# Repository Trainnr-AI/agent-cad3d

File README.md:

# agent-cad3d

Agentic 3D design: describe what you want, and an AI agent builds it in a live Blender session
you can watch and take over at any time. Focused first on robotics: robot links, grippers,
fixtures and simulation scenes, exported to STL/OBJ/glTF and MJCF/URDF.

Built on [MCP for Blender](https://github.com/ahujasid/mcp-for-blender). Other CAD backends
(FreeCAD, SolidWorks) are planned.

**Continuing work? Read [docs/HANDOFF.md](docs/HANDOFF.md).**

## Setup (macOS / Linux / WSL2)

```bash
./scripts/setup.sh
```

This installs `uv` and Blender if missing, installs the MCP for Blender addon and enables it.
Then:

1. Open Blender. The addon's server auto-starts; this repo uses `localhost:9877` (9876 is the trainnr
   Studio viewer's port). Set the port in the addon panel and save it in your .blend. Check it in the 3D viewport:
   press `N` → **MCP for Blender** tab (click **Start MCP Server** if needed).
2. Run `claude` in this repo and approve the `blender` MCP server from `.mcp.json`.
3. Ask for something: *"Make a 2-link planar arm, 0.3 m and 0.25 m links, revolute joints about Z."*

Telemetry is disabled in `.mcp.json`. The addon only listens on localhost.

## How it works

```
you ──▶ Claude Code ──MCP (stdio)──▶ mcp-for-blender ──TCP :9877──▶ Blender addon ──▶ your scene
                ◀────────── screenshots, scene info, results ◀──────────
```

The agent writes Blender Python for modelling, reads numbers back from the scene, and takes
viewport screenshots to check its own work. Conventions it follows are in [CLAUDE.md](CLAUDE.md).

## Security note

The MCP server can run any Python inside Blender. Save your work, and only connect it to Blender
instances you trust. Set `BLENDER_MCP_SAFE_MODE=1` in `.mcp.json`'s `env` to block file, network
and subprocess access from agent scripts (normal modelling and import/export still work).

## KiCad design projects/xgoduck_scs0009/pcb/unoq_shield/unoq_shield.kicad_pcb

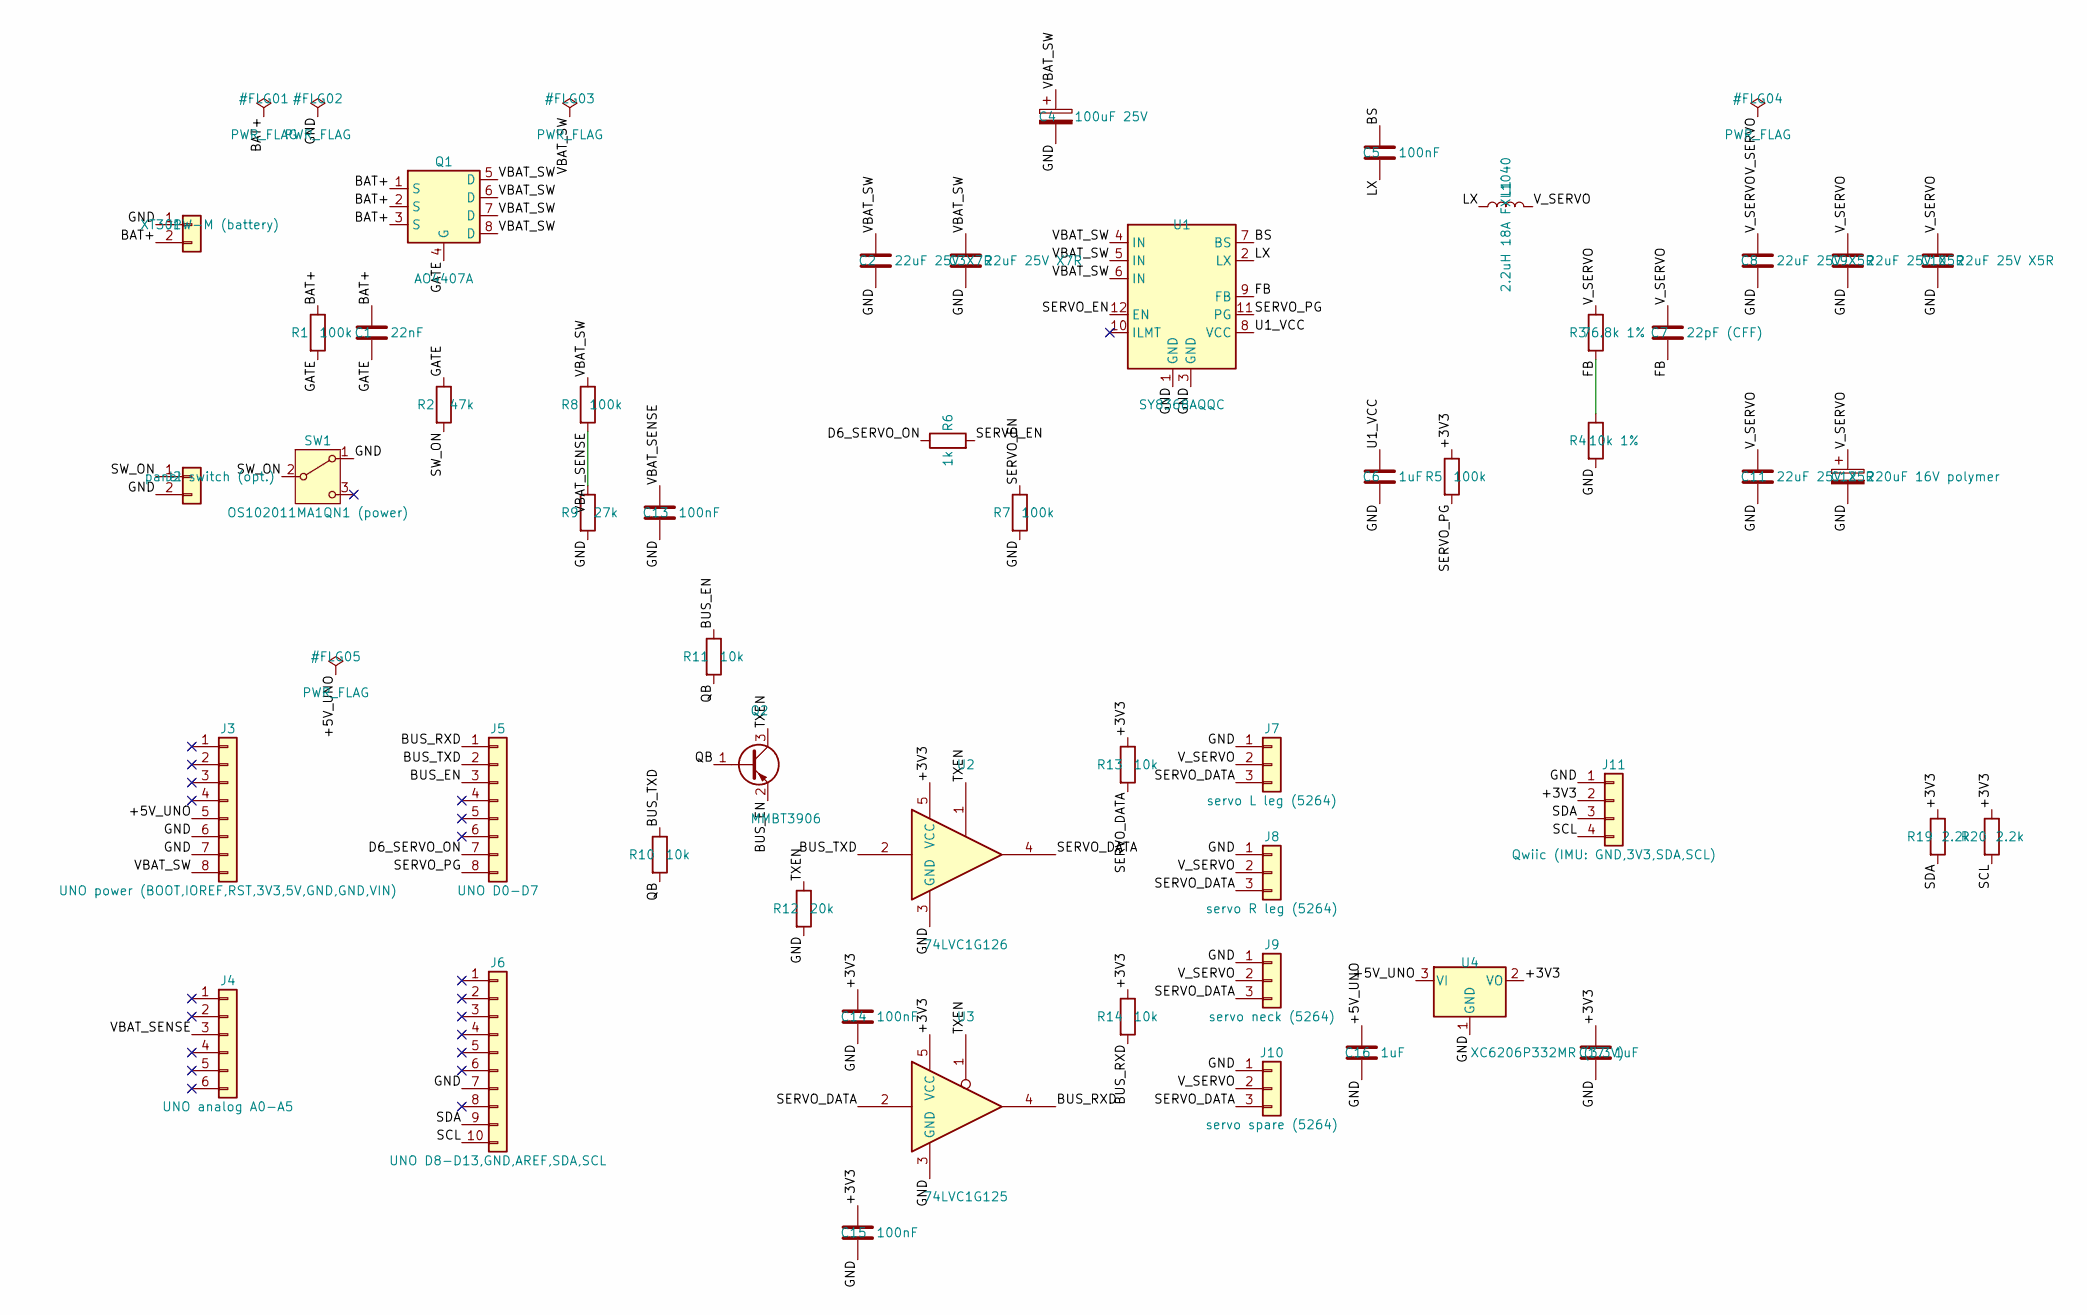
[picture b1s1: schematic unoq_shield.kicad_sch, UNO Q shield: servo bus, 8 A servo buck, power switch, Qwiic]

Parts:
C1: 22nF; C_0603_1608Metric; LCSC C21122
C2, C3: 22uF 25V X7R; C_1206_3216Metric; LCSC C12891
C4: 100uF 25V; CP_Elec_6.3x7.7; LCSC C72477
C5, C13, C14, C15: 100nF; C_0603_1608Metric; LCSC C14663
C6, C16, C17: 1uF; C_0603_1608Metric; LCSC C15849
C7: 22pF (CFF); C_0603_1608Metric; LCSC C1653
C8, C9, C10, C11: 22uF 25V X5R; C_1206_3216Metric; LCSC C12891
C12: 220uF 16V polymer; CP_Elec_6.3x7.7; LCSC C881921
J1: XT30PW-M (battery); AMASS_XT30PW-M_1x02_P2.50mm_Horizontal; LCSC C431092
J2: panel switch (opt.); JST_PH_B2B-PH-K_1x02_P2.00mm_Vertical; LCSC C131337
J3: UNO power (BOOT,IOREF,RST,3V3,5V,GND,GND,VIN); PinHeader_1x08_P2.54mm_Vertical; LCSC C492407
J4: UNO analog A0-A5; PinHeader_1x06_P2.54mm_Vertical; LCSC C492405
J5: UNO D0-D7; PinHeader_1x08_P2.54mm_Vertical; LCSC C492407
J6: UNO D8-D13,GND,AREF,SDA,SCL; PinHeader_1x10_P2.54mm_Vertical; LCSC C492409
J7: servo L leg (5264); Molex_SPOX_5267-03A_1x03_P2.50mm_Vertical; LCSC C2845815
J8: servo R leg (5264); Molex_SPOX_5267-03A_1x03_P2.50mm_Vertical; LCSC C2845815
J9: servo neck (5264); Molex_SPOX_5267-03A_1x03_P2.50mm_Vertical; LCSC C2845815
J10: servo spare (5264); Molex_SPOX_5267-03A_1x03_P2.50mm_Vertical; LCSC C2845815
J11: Qwiic (IMU: GND,3V3,SDA,SCL); JST_SH_SM04B-SRSS-TB_1x04-1MP_P1.00mm_Horizontal; LCSC C160404
L1: 2.2uH 18A FXL1040; L_Changjiang_FXL1040; LCSC C167228
Q1: AO4407A; SOIC-8_3.9x4.9mm_P1.27mm; LCSC C16072
Q2: MMBT3906; SOT-23; LCSC C7420354
R1, R5, R7, R8: 100k; R_0603_1608Metric; LCSC C25803
R2: 47k; R_0603_1608Metric; LCSC C25819
R3: 76.8k 1%; R_0603_1608Metric; LCSC C2930130
R4: 10k 1%; R_0603_1608Metric; LCSC C25804
R6: 1k; R_0603_1608Metric; LCSC C21190
R9: 27k; R_0603_1608Metric; LCSC C22967
R10, R11, R13, R14: 10k; R_0603_1608Metric; LCSC C25804
R12: 20k; R_0603_1608Metric; LCSC C4184
R19, R20: 2.2k; R_0603_1608Metric; LCSC C4190
SW1: OS102011MA1QN1 (power); SW_Slide_SPDT_Angled_CK_OS102011MA1Q; LCSC C226259
U1: SY8368AQQC; SY8368AQQC_QFN3x3-12; LCSC C207642
U2: 74LVC1G126; SOT-23-5; LCSC C7834
U3: 74LVC1G125; SOT-23-5; LCSC C23654
U4: XC6206P332MR (3.3V); SOT-23; LCSC C5446

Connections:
/+3V3: C14.1, C15.1, C17.1, J11.2, R5.1, R13.1, R14.1, R19.1, R20.1, U2.5 (VCC), U3.5 (VCC), U4.2 (VO)
/+5V_UNO: C16.1, J3.5, U4.3 (VI)
/BAT+: C1.1, J1.2, Q1.1 (S), Q1.2 (S), Q1.3 (S), R1.1
/BS: C5.1, U1.7 (BS)
/BUS_EN: J5.3, Q2.2 (E), R11.1
/BUS_RXD: J5.1, R14.2, U3.4
/BUS_TXD: J5.2, R10.1, U2.2
/D6_SERVO_ON: J5.7, R6.1
/FB: C7.2, R3.2, R4.1, U1.9 (FB)
/GATE: C1.2, Q1.4 (G), R1.2, R2.1
/GND: C2.2, C3.2, C4.2, C6.2, C8.2, C9.2, C10.2, C11.2, C12.2, C13.2, C14.2, C15.2, C16.2, C17.2, J1.1, J2.2, J3.6, J3.7, J6.7, J7.1, J8.1, J9.1, J10.1, J11.1, R4.2, R7.2, R9.2, R12.2, SW1.1 (A), U1.1 (GND), U1.3 (GND), U2.3 (GND), U3.3 (GND), U4.1 (GND)
/LX: C5.2, L1.1, U1.2 (LX)
/QB: Q2.1 (B), R10.2, R11.2
/SCL: J6.10, J11.4, R20.2
/SDA: J6.9, J11.3, R19.2
/SERVO_DATA: J7.3, J8.3, J9.3, J10.3, R13.2, U2.4, U3.2
/SERVO_EN: R6.2, R7.1, U1.12 (EN)
/SERVO_PG: J5.8, R5.2, U1.11 (PG)
/SW_ON: J2.1, R2.2, SW1.2 (B)
/TXEN: Q2.3 (C), R12.1, U2.1, U3.1
/U1_VCC: C6.1, U1.8 (VCC)
/VBAT_SENSE: C13.1, J4.3, R8.2, R9.1
/VBAT_SW: C2.1, C3.1, C4.1, J3.8, Q1.5 (D), Q1.6 (D), Q1.7 (D), Q1.8 (D), R8.1, U1.4 (IN), U1.5 (IN), U1.6 (IN)
/V_SERVO: C7.1, C8.1, C9.1, C10.1, C11.1, C12.1, J7.2, J8.2, J9.2, J10.2, L1.2, R3.1

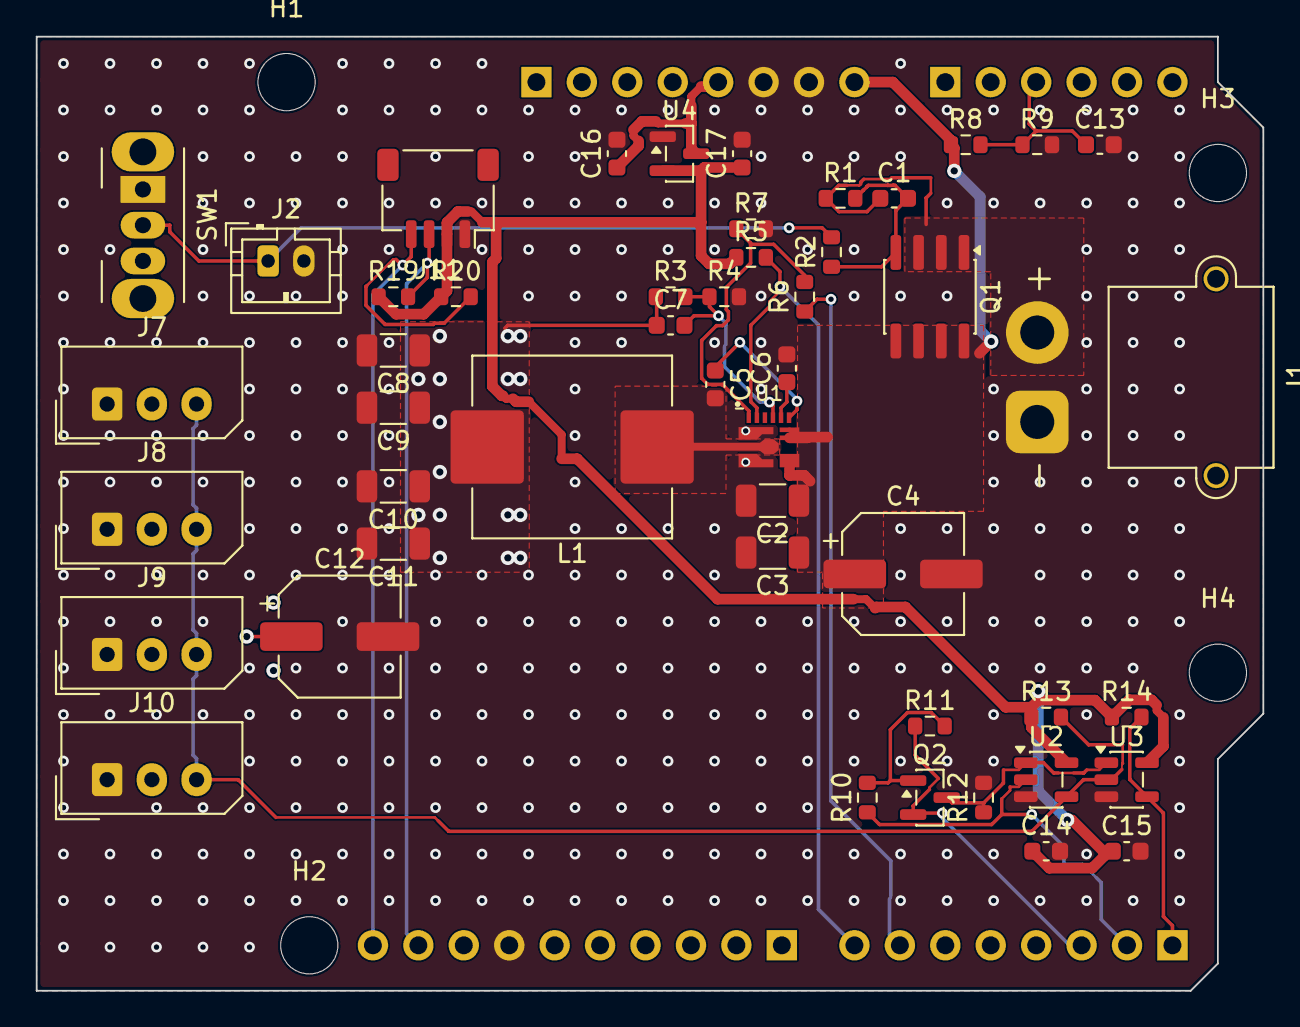
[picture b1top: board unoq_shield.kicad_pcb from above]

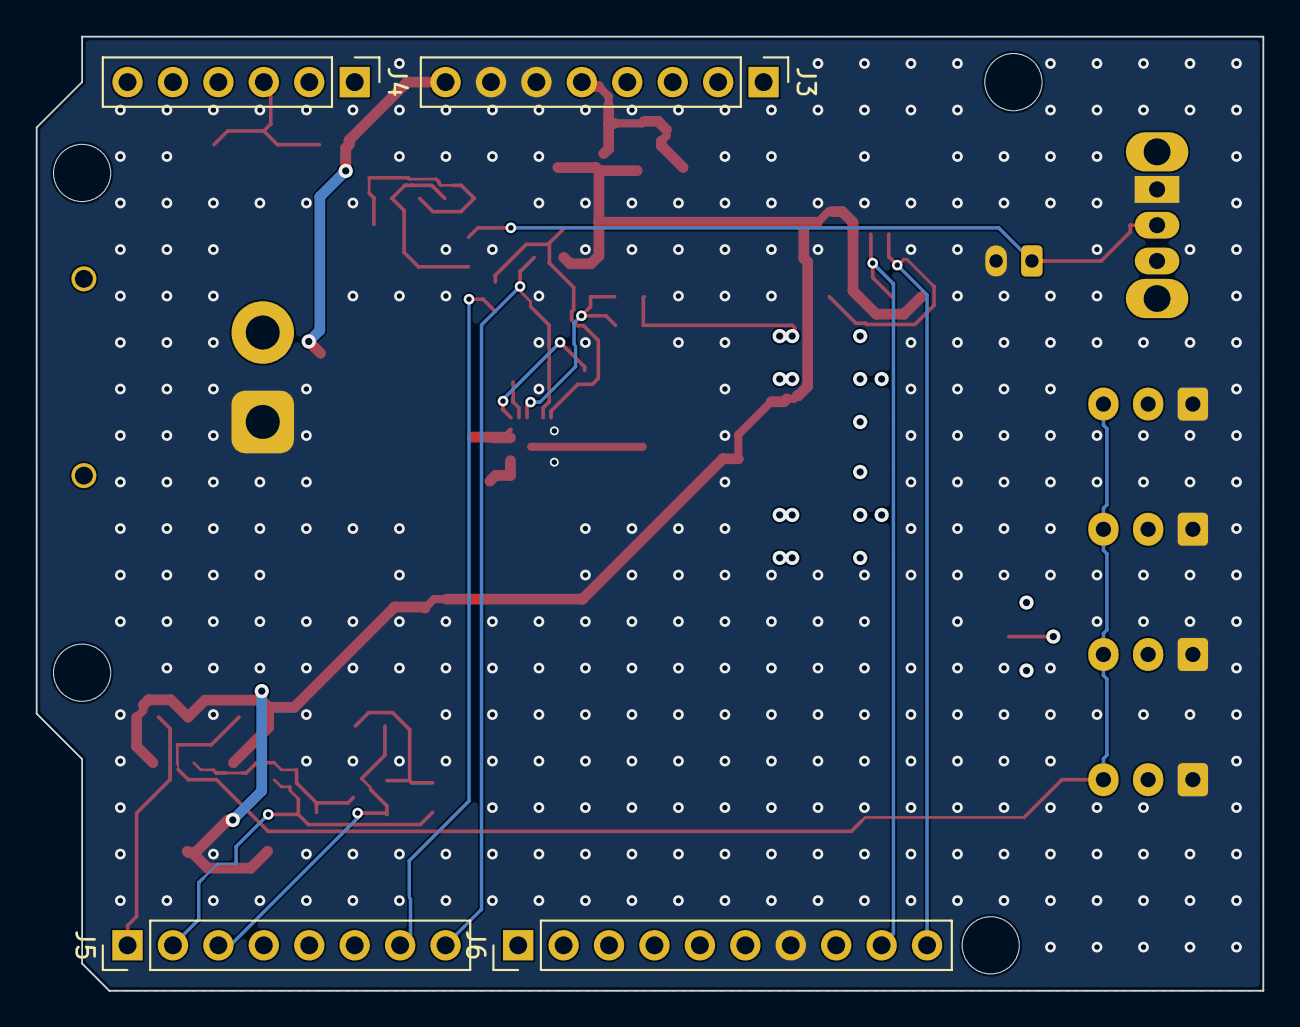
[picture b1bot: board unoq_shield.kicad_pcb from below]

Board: 4 copper layers, 68.6 x 53.3 mm, 56 parts (4 on the bottom side), 24 nets.

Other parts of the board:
H1, H2, H3, H4: MountingHole_3.2mm_M3

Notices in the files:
parts and their libraries:
License: Apache-2.0
